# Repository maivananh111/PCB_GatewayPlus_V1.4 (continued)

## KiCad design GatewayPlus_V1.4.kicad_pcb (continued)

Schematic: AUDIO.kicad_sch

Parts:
C60, C113, C116: 1nF; C_0603
C103, C106, C112, C115, C117, C120: 4.7uF; C_0603
C104, C108, C109, C110, C111: 1uF; C_0603
C105, C107, C114, C118, C119: 100nF; C_0603
J9: AudioJack; AudioJack_3.5mm_PJ-320A
L13: 2nH; L_0603
R58, R59, R60: 1k; R_0603
R61, R64, R65: 10k; R_0603
R62, R63, R66: 10; R_0603
U9: ES8388; QFN-28_4x4_PAD-VIAS

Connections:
/AUDIO/EMIC: C60.2, C108.1, C109.1, J9.S, R61.2
/AUDIO/LOUT: J9.T, R62.2, R65.2
/AUDIO/LRCLK: U9.7 (LRCK); also elsewhere on the board
/AUDIO/MCLK: U9.1 (MCLK); also elsewhere on the board
/AUDIO/ROUT: J9.R1, R63.2, R64.2
/AUDIO/SCL: R58.1, U9.28 (CCLK); also elsewhere on the board
/AUDIO/SCLK: U9.5 (SCLK); also elsewhere on the board
/AUDIO/SDA: R59.1, U9.27 (CDATA); also elsewhere on the board
/AUDIO/SDIN: U9.6 (SDIN); also elsewhere on the board
/AUDIO/SDOUT: U9.8 (ASDOUT)
GND: C60.1, C103.1, C104.1, C105.1, C106.1, C107.1, C112.1, C113.1, C114.1, C115.1, C116.1, C117.1, C118.1, C119.1, C120.1, J9.R2, R60.2, R61.1, R64.1, R65.1, U9.4 (DGND), U9.13 (HPGND), U9.18 (AGND), U9.29 (PAD); also elsewhere on the board
unnamed: C110.1, C116.2, R62.1
unnamed: C111.1, C113.2, R63.1
unnamed: C117.2, C118.2, R66.1, U9.17 (AVDD)
unnamed: R60.1, U9.26 (CE/ADDR)
unnamed: C119.2, C120.2, U9.19 (DACVREF)
unnamed: C103.2, C105.2, L13.2, U9.2 (DVDD), U9.3 (PVDD)
unnamed: C108.2, U9.24 (LIN1)
unnamed: C110.2, U9.12 (LOUT1)
unnamed: C109.2, U9.23 (RIN1)
unnamed: C111.2, U9.11 (ROUT1)
unnamed: C114.2, C115.2, U9.20 (VMID)
unnamed: C106.2, C107.2, U9.10 (VREF)

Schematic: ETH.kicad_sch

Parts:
C36, C37: 10pF; C_0603
C52, C59: 10nF/1KV; C_1206
C79, C83, C88: 10nF; C_0603
C80: 1uF; C_0603
C81, C82, C84, C87: 100nF; C_0603
C85, C86: C_Small; C_0603
J6: HR911105A; RJ45_Hanrun_HR911105A
JP12: PHYADDR; Jump3_0603_Open
L10: 2nH; L_0603
R23, R24, R30, R32: 10k; R_0603
R28: 12k; R_0603
R29, R31, R33, R34: 49.9; R_0603
R35, R36: 220; R_0603
R80: 33; R_0603
R81: 1M/1W; R_1206
U7: LAN8720A; QFN-24_4x4mm_PAD-VIAS
Y4: 25MHz; Crystal_SMD_3225-4Pin_3.2x2.5mm

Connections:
/ETH/ETH_REFCLK: R80.1; also elsewhere on the board
/ETH/RMII_CRS_DV: U7.11 (CRS_DV/MODE2); also elsewhere on the board
/ETH/RMII_MDC: U7.13 (MDC); also elsewhere on the board
/ETH/RMII_MDIO: R23.2, U7.12 (MDIO); also elsewhere on the board
/ETH/RMII_RXD0: U7.8 (RXD0/MODE0); also elsewhere on the board
/ETH/RMII_RXD1: U7.7 (RXD1/MODE1); also elsewhere on the board
/ETH/RMII_TXD0: U7.17 (TXD0); also elsewhere on the board
/ETH/RMII_TXD1: U7.18 (TXD1); also elsewhere on the board
/ETH/RMII_TXEN: U7.16 (TXEN); also elsewhere on the board
/ETH/RX_N: J6.6, R29.2, U7.22 (RXN)
/ETH/RX_P: J6.3, R31.2, U7.23 (RXP)
/ETH/TX_N: J6.2, R33.2, U7.20 (TXN)
/ETH/TX_P: J6.1, R34.2, U7.21 (TXP)
Earth: C52.1, C59.2, J6.SH (SHIELD), R81.1; also elsewhere on the board
GND: C36.1, C37.1, C59.1, C79.1, C80.1, C81.1, C82.1, C83.1, C84.1, C85.1, C86.1, C87.1, C88.1, J6.8, J6.10, J6.11, JP12.1 (A), R28.2, R30.2, R32.2, R81.2, U7.25 (VSS), Y4.2, Y4.4; also elsewhere on the board
unnamed: J6.9, R35.2
unnamed: J6.12, R36.2
unnamed: JP12.2 (C), U7.10 (RXER/PHYAD0)
unnamed: R80.2, U7.14 (INT/REFCLKO)
unnamed: R32.1, R36.1, U7.3 (LED1/REGOFF)
unnamed: R30.1, R35.1, U7.2 (LED2/nINTSEL)
unnamed: R28.1, U7.24 (RBIAS)
unnamed: C79.2, R24.2, U7.15 (RST)
unnamed: C85.2, C86.2, L10.2, U7.1 (VDD2A), U7.19 (VDD1A)
unnamed: C83.2, C84.2, U7.6 (VDDCR)
unnamed: C36.2, U7.5 (XTAL1/CLKIN), Y4.3
unnamed: C37.2, U7.4 (XTAL2), Y4.1

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
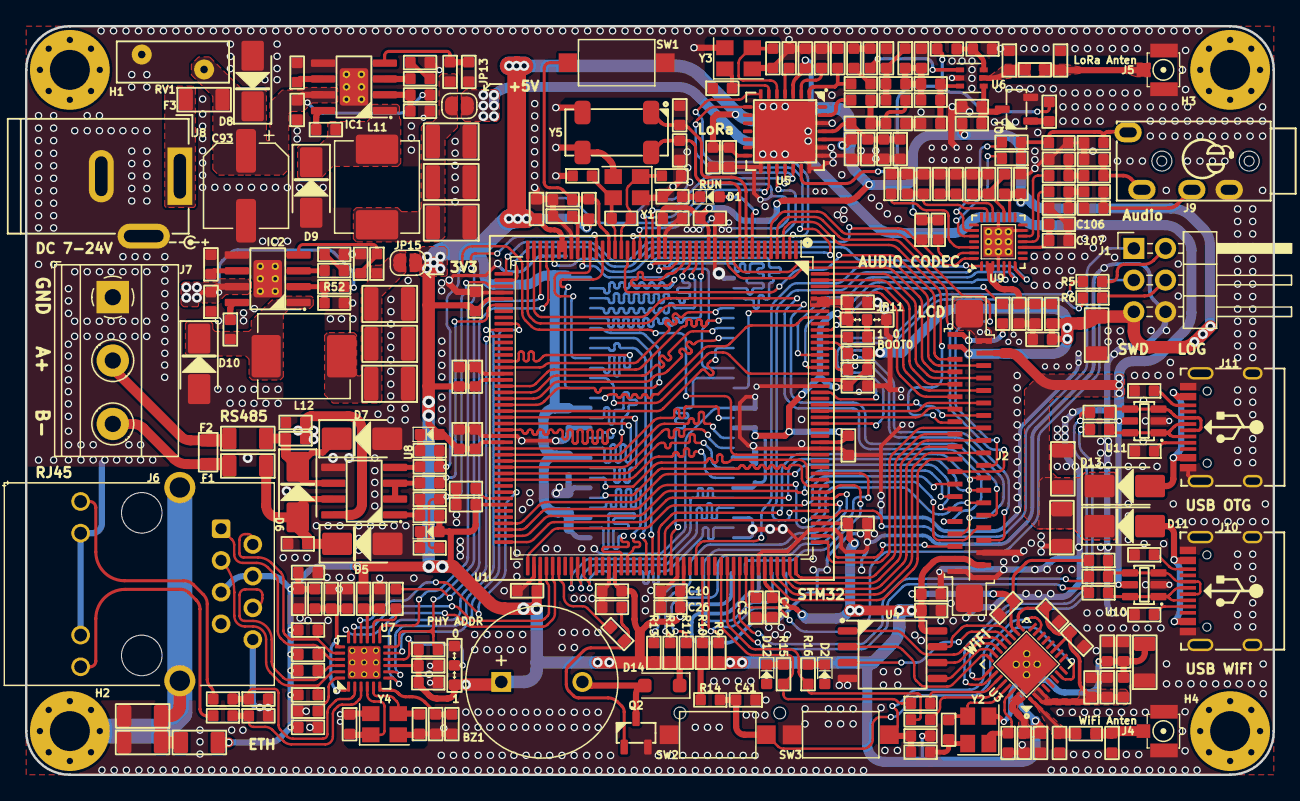
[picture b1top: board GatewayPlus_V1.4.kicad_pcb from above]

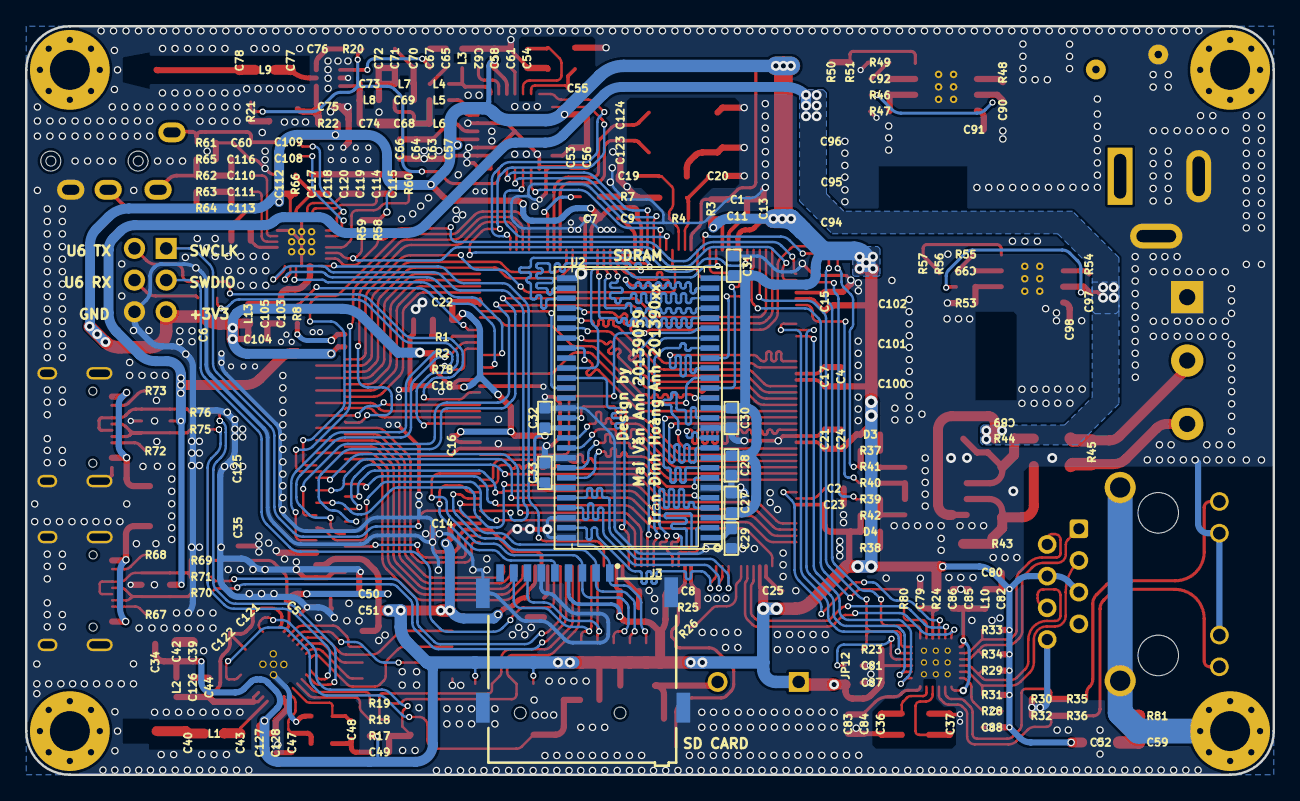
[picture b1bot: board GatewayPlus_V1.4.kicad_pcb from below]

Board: 2 copper layers, 100.0 x 60.0 mm, 276 parts (9 on the bottom side), 236 nets.

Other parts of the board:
C35, C125: 10uF; C_1206

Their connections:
GND: C35.1, C125.1; also elsewhere on the board

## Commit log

2023-02-28 Finish routing.
2023-02-28 Fix some bug.
2023-03-02 Finished Board.
2023-03-02 Finish board.
2023-03-03 OKE.
2023-03-03 Finish.
2023-03-05 Add power LED and some Silkscreen text.
2023-03-07 None.
2023-04-14 Fix USB silkscreen name.
